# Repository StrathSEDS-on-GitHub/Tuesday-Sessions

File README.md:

# Tuesday-Sessions
Repositories for Tuesday session files

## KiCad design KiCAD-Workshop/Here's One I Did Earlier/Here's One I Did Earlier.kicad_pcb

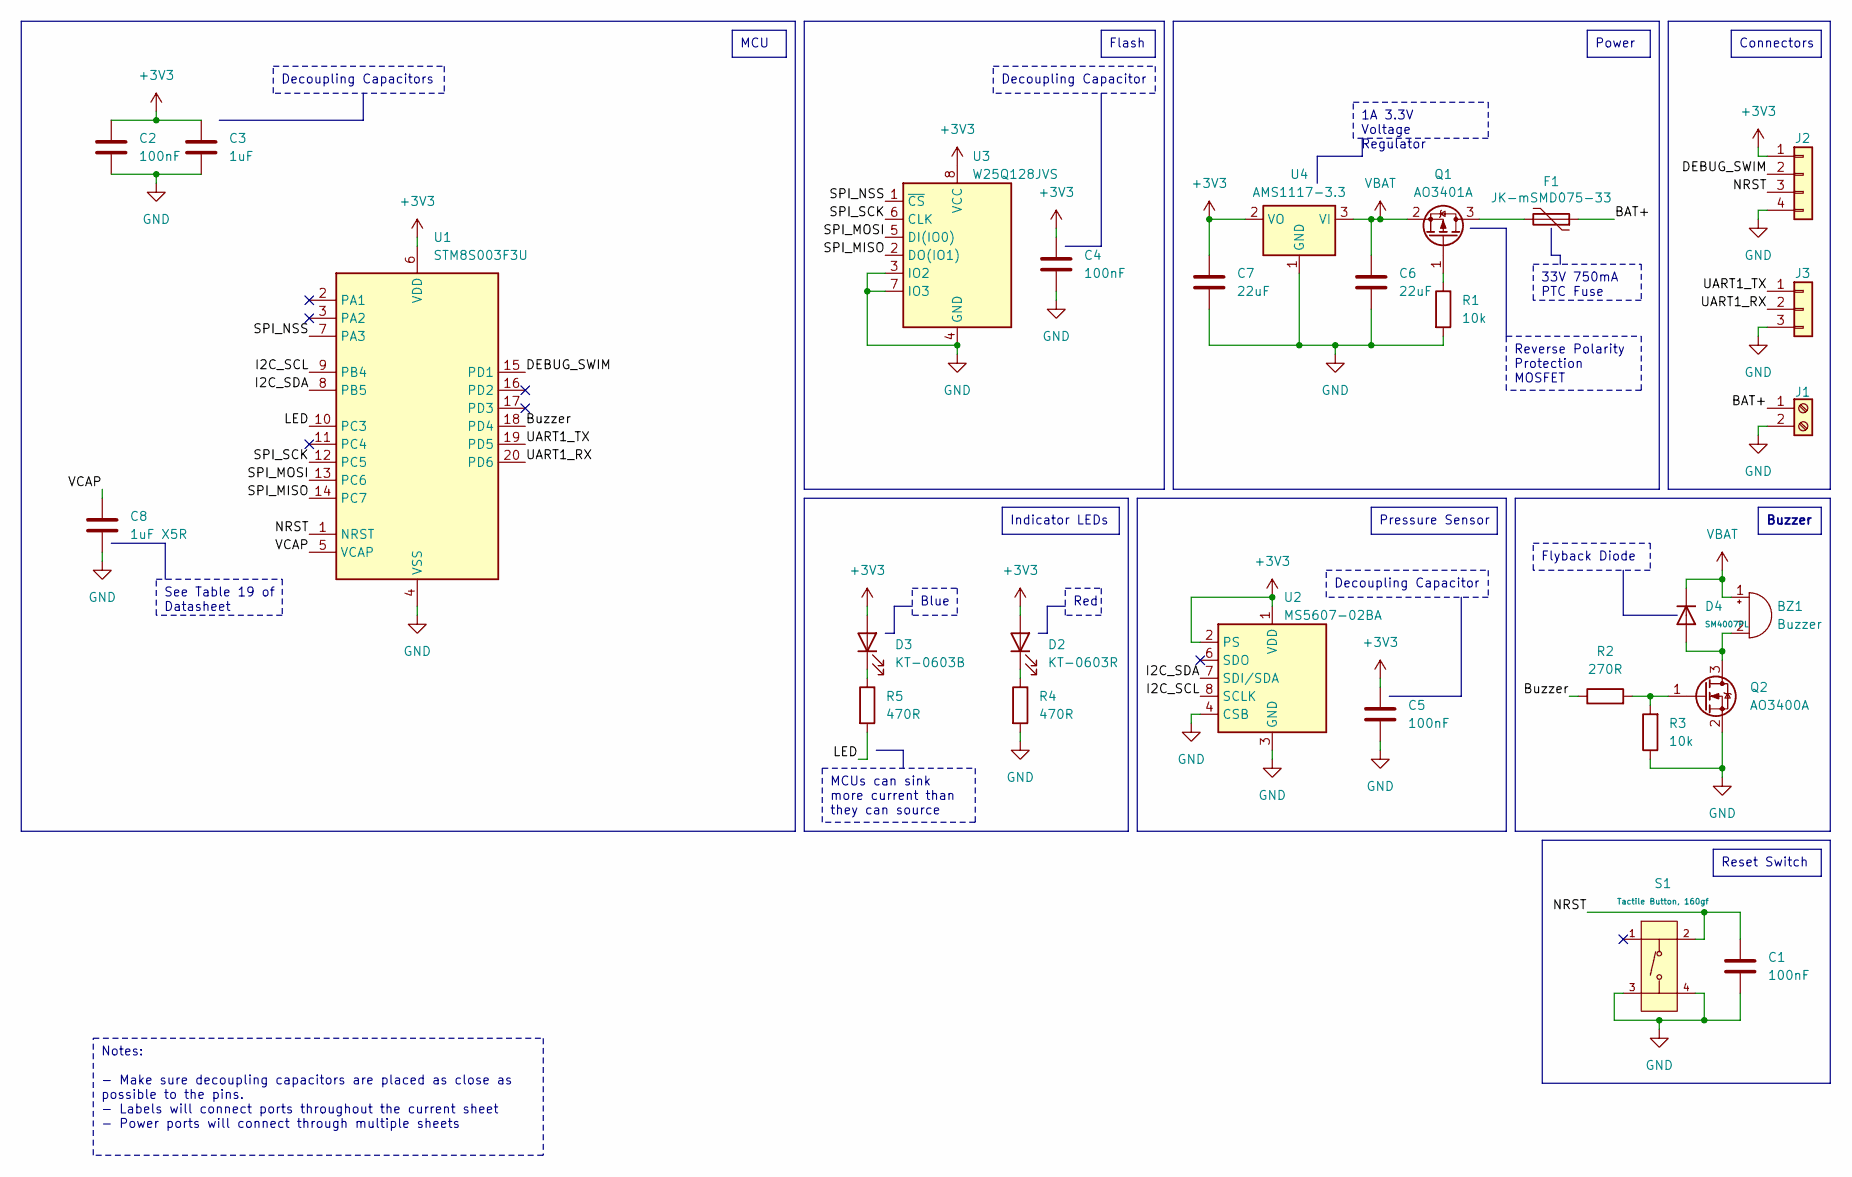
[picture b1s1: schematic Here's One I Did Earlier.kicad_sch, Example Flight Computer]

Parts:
BZ1: Buzzer; MagneticBuzzer_Kingstate_KCG0601
C1, C2, C4, C5: 100nF; C_0603_1608Metric
C3: 1uF; C_0603_1608Metric
C6, C7: 22uF; C_0603_1608Metric
C8: 1uF X5R; C_0603_1608Metric
D2: KT-0603R; LED_0603_1608Metric
D3: KT-0603B; LED_0603_1608Metric
D4: SM4007PL; D_SOD-123FL; Forward Voltage (Vf@If) 1.1V@1A; Reverse Voltage (Vr) 1kV; Part SM4007PL; LCSC C64898
F1: JK-mSMD075-33; Fuse_1812_4532Metric
J1: Screw Terminal
J2: Debug Header; PinHeader_1x04_P2.54mm_Vertical
J3: UART Header; PinHeader_1x03_P1.00mm_Vertical
Q1: AO3401A; SOT-23
Q2: AO3400A; SOT-23
R1, R3: 10k; R_0603_1608Metric
R2: 270R; R_0603_1608Metric
R4, R5: 470R; R_0603_1608Metric
S1: Tactile Button, 160gf; SW-SMD_4P-L5.1-W5.1-P3.70-LS6.5-TL-2; Voltage Rating (Dc) 12V; Part TS-1187A-B-A-B; LCSC C318884
U1: STM8S003F3U; ST_UFQFPN-20_3x3mm_P0.5mm
U2: MS5607-02BA; LGA-8_3x5mm_P1.25mm
U3: W25Q128JVS; SOIC-8_5.23x5.23mm_P1.27mm
U4: AMS1117-3.3; SOT-223-3_TabPin2

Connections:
+3V3: C2.1, C3.1, C4.1, C5.1, C7.1, D2.2 (A), D3.2 (A), J2.1, U1.6 (VDD), U2.1 (VDD), U2.2 (PS), U3.8 (VCC), U4.2 (VO)
/BAT+: F1.1, J1.1
/Buzzer: R2.1, U1.18 (PD4)
/DEBUG_SWIM: J2.2, U1.15 (PD1)
/I2C_SCL: U1.9 (PB4), U2.8 (SCLK)
/I2C_SDA: U1.8 (PB5), U2.7 (SDI/SDA)
/LED: R5.2, U1.10 (PC3)
/NRST: C1.1, J2.3, S1.2 (B), U1.1 (NRST)
/SPI_MISO: U1.14 (PC7), U3.2 (DO(IO1))
/SPI_MOSI: U1.13 (PC6), U3.5 (DI(IO0))
/SPI_NSS: U1.7 (PA3), U3.1 (~CS)
/SPI_SCK: U1.12 (PC5), U3.6 (CLK)
/UART1_RX: J3.2, U1.20 (PD6)
/UART1_TX: J3.1, U1.19 (PD5)
/VCAP: C8.1, U1.5 (VCAP)
GND: C1.2, C2.2, C3.2, C4.2, C5.2, C6.2, C7.2, C8.2, J1.2, J2.4, J3.3, Q2.2 (S), R1.2, R3.1, R4.2, S1.3 (C), S1.4 (D), U1.4 (VSS), U2.3 (GND), U2.4 (CSB), U2.5 (CSB), U3.3 (IO2), U3.4 (GND), U3.7 (IO3), U4.1 (GND)
unnamed: BZ1.2 (-), D4.2, Q2.3 (D)
unnamed: D2.1 (K), R4.1
unnamed: D3.1 (K), R5.1
unnamed: F1.2, Q1.3 (D)
unnamed: Q1.1 (G), R1.1
unnamed: Q2.1 (G), R2.2, R3.2
VBAT: BZ1.1 (+), C6.1, D4.1, Q1.2 (S), U4.3 (VI)

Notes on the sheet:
MCUs can sink more current than they can source
Decoupling Capacitors
1A 3.3V Voltage Regulator
Reset Switch
Indicator LEDs
Reverse Polarity Protection MOSFET
Buzzer
Notes: - Make sure decoupling capacitors are placed as close as possible to the pins. - Labels will connect ports throughout the current sheet - Power ports will connect through multiple sheets
See Table 19 of Datasheet
Power
Connectors
33V 750mA PTC Fuse
Blue
MCU
Flash
Decoupling Capacitor
Pressure Sensor
Flyback Diode
Red

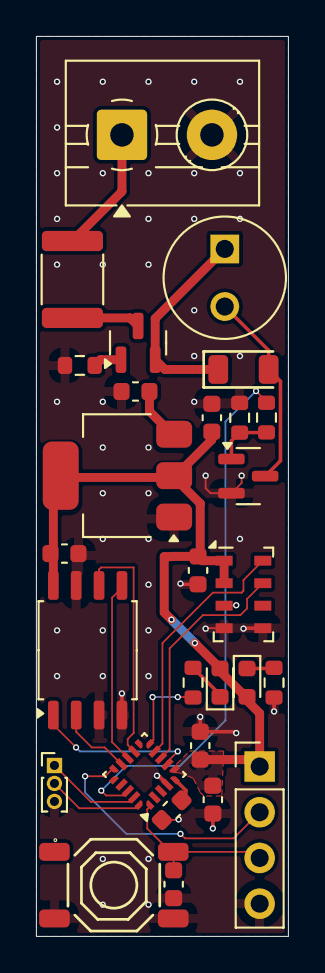
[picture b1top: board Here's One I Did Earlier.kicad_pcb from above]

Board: 2 copper layers, 14.0 x 50.0 mm, 28 parts (0 on the bottom side), 23 nets.

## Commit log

2025-01-25 Created Schematic
    - Added File Structure
    - Created Schematic
2025-01-25 Fnished Example PCB
    Routed PCB
    Fixed many DRC
